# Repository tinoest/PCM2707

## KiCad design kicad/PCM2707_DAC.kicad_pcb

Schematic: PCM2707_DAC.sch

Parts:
C1, C3, C7, C9, C12: 1uF; PASSIVES_0805
C2: 10uF; PASSIVES_PANASONIC_C
C4, C5: 22pF; PASSIVES_0805
C6, C8: 22nF; PASSIVES_0805
C10, C11: 100uF; PASSIVES_PANASONIC_D
CON1: GND_CONNECTORSMD; GND_CONNECTOR
DOUT1: 87758-0216; CON-MOLEX_87758-0216
J1: USB; MOLEX-47346-0001_MOLEX_47346-0001
JACK-OUT1: STEREOJACK; STX3100
JP1: CONNECTORS_1X05_LOCK
L1: 1A FB; PASSIVES_0805
LED1, LED2: Blue; LED_LED-0603
OUTPUT1: AUDIO; CON-LSTB_MA03-1
Q1: 12MHz; CRYSTAL_HC49U-V
R1: 1MOhm; PASSIVES_0805
R2, R4: 16Ohm; PASSIVES_0805
R3, R11: 1.5kOhm; PASSIVES_0805
R5, R6, R8, R10: 3.3kOhm; PASSIVES_0805
R7, R9: 22Ohm; PASSIVES_0805
R12: 560Ohm; PASSIVES_0805
R13: 330Ohm; PASSIVES_0805
SV1: USB-WIRE; CON-LSTB_MA04-1
U1: PCM2707C

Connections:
5V: C12.1, JP1.2, L1.1, LED1.1, U1.24 (VBUS)
//SSPND: LED2.1, U1.11 (SSPND)
/D+: J1.3, R9.2, R11.1, SV1.3
/D-: J1.2, R7.2, SV1.2
/N$1: JP1.5, U1.6 (HID0)
/N$2: C1.2, U1.2 (VCCP)
/N$3: JP1.4, U1.7 (HID1)
/N$4: C2.+, U1.32 (VCOM)
/N$5: JP1.3, U1.8 (HID2)
/N$6: DOUT1.1, U1.17 (DOUT)
/N$7: C4.1, Q1.1, R1.1, U1.12 (XTI)
/N$8: C5.1, Q1.2, R1.2, U1.13 (XTO)
/N$9: R9.1, U1.23 (D+)
/N$10: R7.1, U1.22 (D-)
/N$13: C3.2, U1.30 (VCCR)
/N$14: LED1.2, R12.2
/N$15: R3.2, U1.15 (DT)
/N$16: C7.1, U1.27 (VCCL)
/N$17: C8.2, R4.2
/N$18: C6.2, R2.2
/N$21: C8.1, C11.+, R6.2, U1.29 (VOUTR)
/N$22: LED2.2, R13.2
/N$23: C6.1, C10.+, R5.2, U1.28 (VOUTL)
/VBUS: J1.1, L1.2, SV1.1
AGND: C3.1, C7.2, CON1.1 (AGND), JACK-OUT1.1, OUTPUT1.1, R2.1, R4.1, R5.1, R6.1, R8.1, R10.1, U1.25 (ZGND+), U1.26 (AGNDL), U1.31 (AGNDR)
GND: C1.1, C2.-, C4.2, C5.2, C9.2, C12.2, CON1.2 (DGND), DOUT1.2, J1.5, JP1.1, R12.1, R13.1, SV1.4, U1.1 (PGND), U1.3 (HOST), U1.20 (DGND)
OL: C10.-, JACK-OUT1.5, OUTPUT1.3, R8.2
OR: C11.-, JACK-OUT1.2, OUTPUT1.2, R10.2
VDD: C9.1, R3.1, R11.2, U1.9 (FSEL), U1.10 (TEST), U1.16 (PSEL), U1.21 (VDD)

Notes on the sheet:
VDD
/SSPND
VBUS
GND

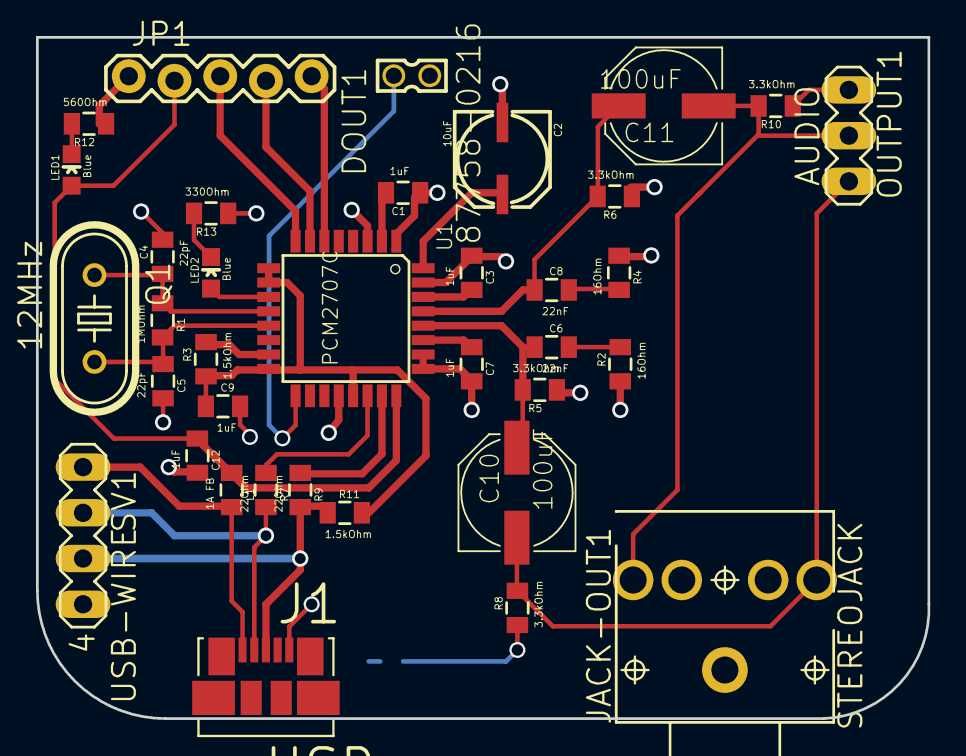
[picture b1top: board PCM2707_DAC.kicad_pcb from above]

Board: 2 copper layers, 49.5 x 37.8 mm, 37 parts (0 on the bottom side), 29 nets.

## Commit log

2016-12-10 PCM2707 DAC Design
    Simple first check in of logic
2017-03-19 Added Gerber Files
    Created Gerber Data
2017-03-19 Added updated files, and PDF of data
2017-03-19 Added Component List
2017-03-24 Adding kicad files
2017-03-25 Added MOD file
2017-03-25 Modified kicad files and corrected errors
2017-03-25 Modified and matched footprints
2017-03-25 Updated Schematic to use exported Eagle lbw
2017-03-25 Adding modified files
2017-03-25 Tidied up names, corrected PCB footprint
2017-03-25 Removed not required .lbr
2017-03-25 Removed library prefix from library files
2017-03-25 Rounded corners on design, adding kicad generated berbers
2017-03-25 Revert "Rounded corners on design, adding kicad generated berbers"
    This reverts commit da9f95aa9fce01ce657d28d8956f70ecfce44641.
2017-03-25 Revert "Revert "Rounded corners on design, adding kicad generated gerbers""
    This reverts commit e5d359f14d2e2aadcde64fe7d354a7193523fc92.
2017-04-07 Corrected Crystal Part #
2017-11-08 Converted Libs
    Converted PCM2707 libs from legacy to new version
2017-11-08 Removed .txt and .bak files
2017-11-08 Moved zip of gerbers to gerbers folder
2020-05-16 Updated gitignore

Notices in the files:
parts and their libraries:
SparkFun-Aesthetics: Licensing: Creative Commons ShareAlike 4.0 International - https://creativecommons.org/licenses/by-sa/4.0
